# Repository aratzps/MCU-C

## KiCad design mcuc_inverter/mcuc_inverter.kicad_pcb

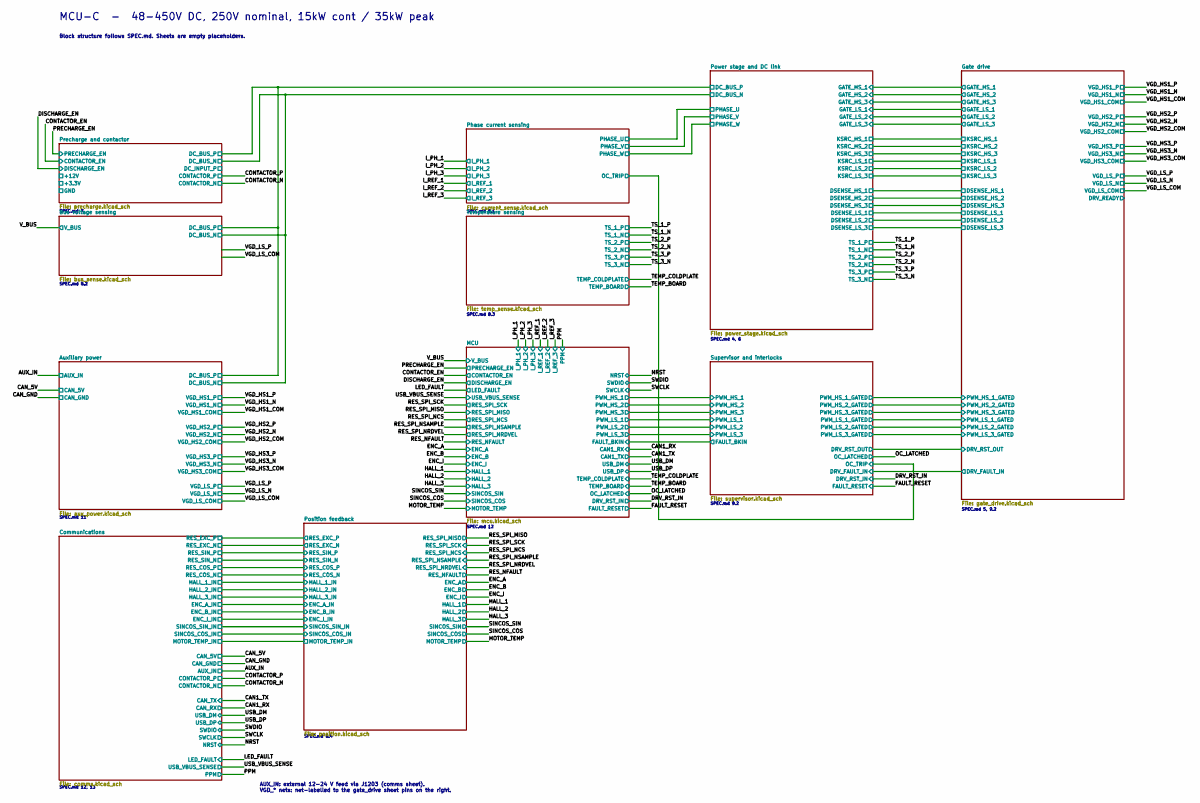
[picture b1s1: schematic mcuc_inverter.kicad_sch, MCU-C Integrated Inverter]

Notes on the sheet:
MCU-C - 48-450V DC, 250V nominal, 15kW cont / 35kW peak
Block structure follows SPEC.md. Sheets are empty placeholders.
SPEC.md 4, 6
SPEC.md 5, 9.2
SPEC.md 7
SPEC.md 8.1
SPEC.md 8.2
SPEC.md 8.3
SPEC.md 8.4
SPEC.md 9.2
SPEC.md 11
SPEC.md 12
SPEC.md 12, 13
AUX_IN: external 12-24 V feed via J1203 (comms sheet). VGD_* nets: net-labelled to the gate_drive sheet pins on the right.

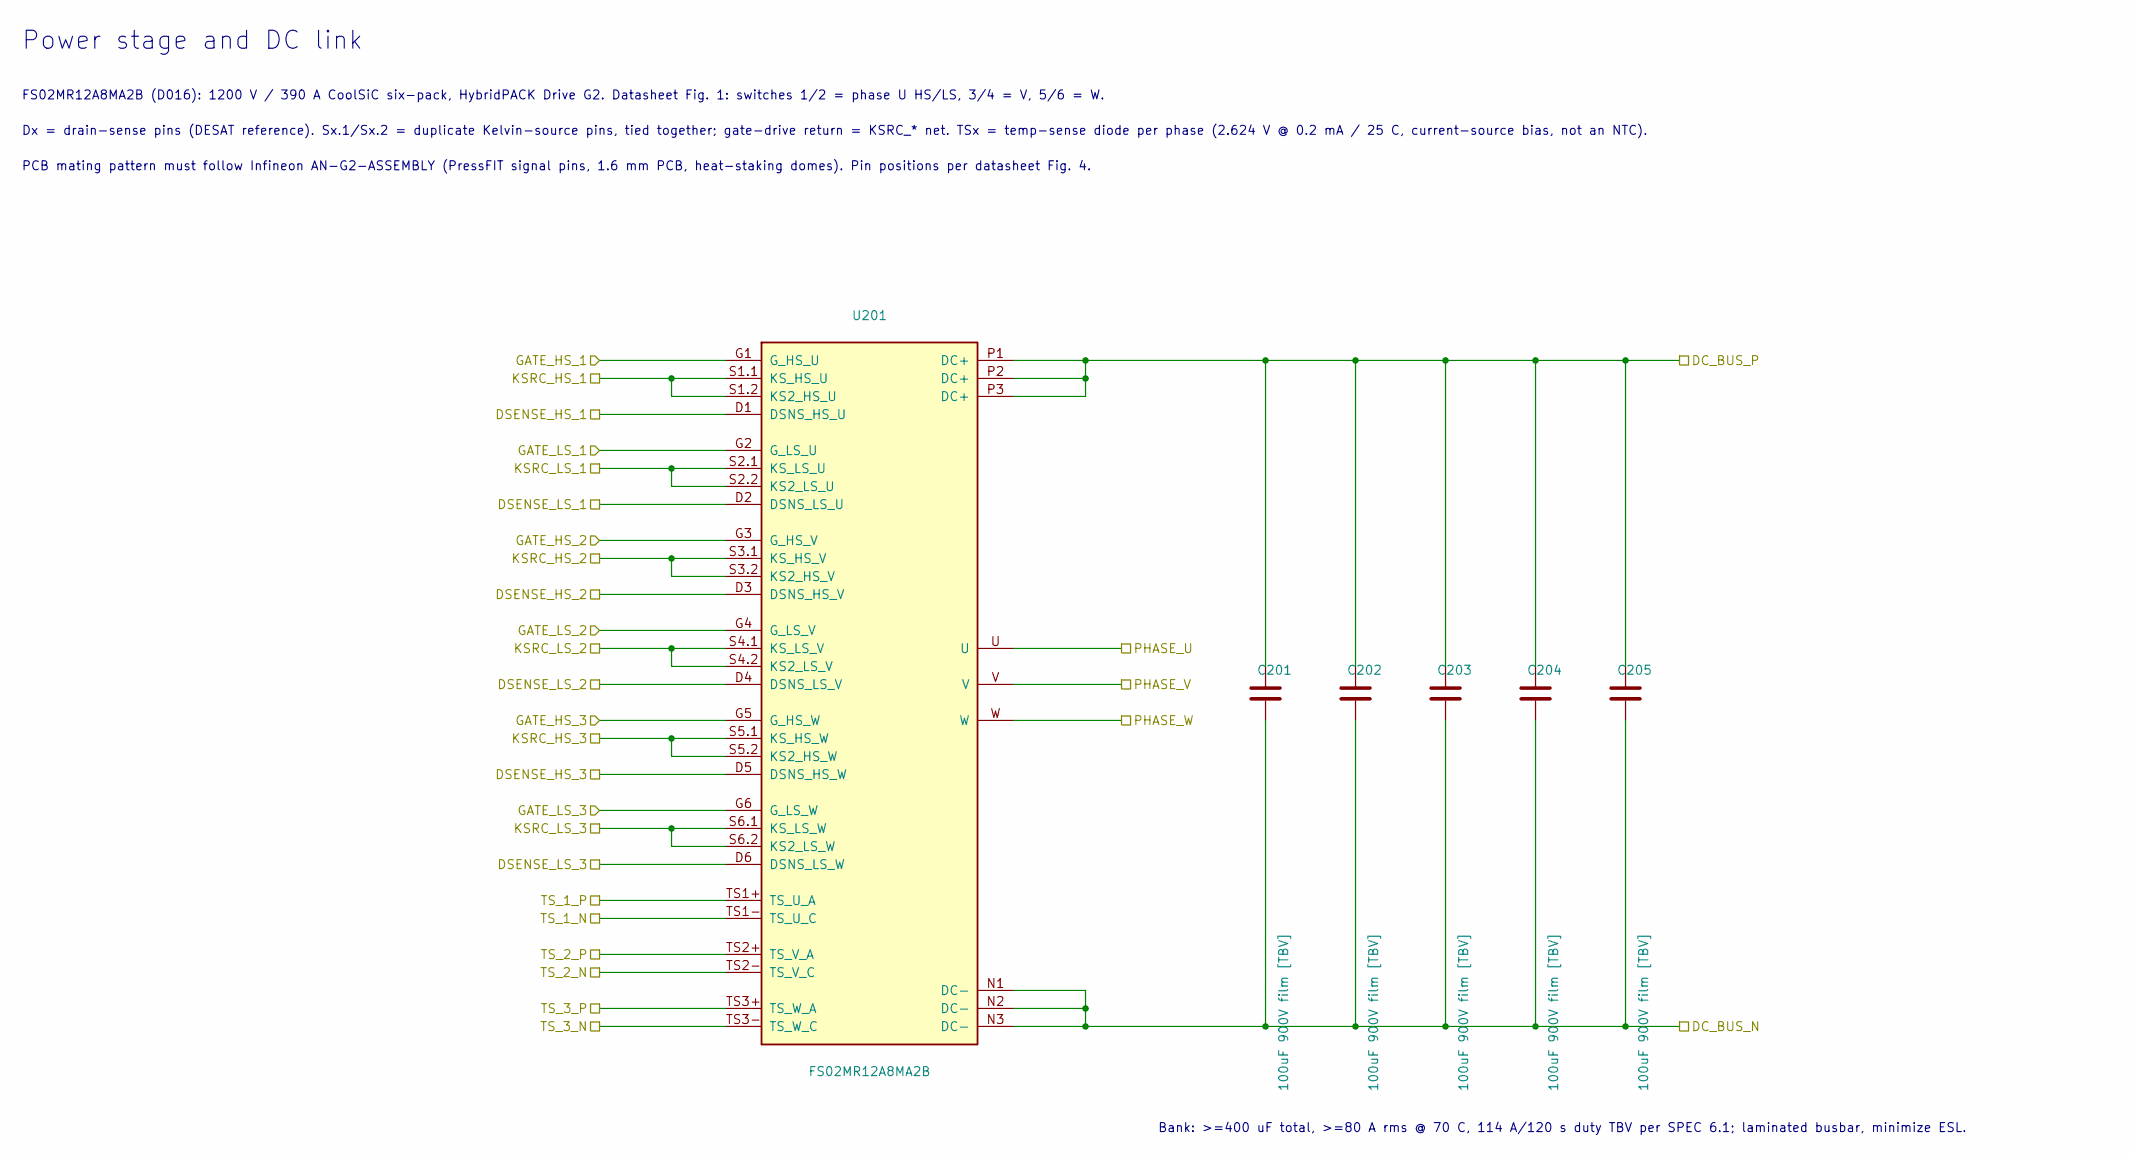
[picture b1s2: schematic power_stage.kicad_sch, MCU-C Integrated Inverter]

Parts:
C201, C202, C203, C204, C205: 100uF 900V film [TBV]; MKP1848C_6pin_52.5x20.3
U201: FS02MR12A8MA2B; FS02MR12A8MA2B_PressFIT

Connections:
/Gate drive/DSENSE_HS_1: U201.D1 (DSNS_HS_U); also elsewhere on the board
/Gate drive/DSENSE_HS_2: U201.D3 (DSNS_HS_V); also elsewhere on the board
/Gate drive/DSENSE_HS_3: U201.D5 (DSNS_HS_W); also elsewhere on the board
/Gate drive/DSENSE_LS_1: U201.D2 (DSNS_LS_U); also elsewhere on the board
/Gate drive/DSENSE_LS_2: U201.D4 (DSNS_LS_V); also elsewhere on the board
/Gate drive/DSENSE_LS_3: U201.D6 (DSNS_LS_W); also elsewhere on the board
/Gate drive/GATE_HS_1: U201.G1 (G_HS_U); also elsewhere on the board
/Gate drive/GATE_HS_2: U201.G3 (G_HS_V); also elsewhere on the board
/Gate drive/GATE_HS_3: U201.G5 (G_HS_W); also elsewhere on the board
/Gate drive/GATE_LS_1: U201.G2 (G_LS_U); also elsewhere on the board
/Gate drive/GATE_LS_2: U201.G4 (G_LS_V); also elsewhere on the board
/Gate drive/GATE_LS_3: U201.G6 (G_LS_W); also elsewhere on the board
/TS_1_N: U201.TS1- (TS_U_C); also elsewhere on the board
/TS_1_P: U201.TS1+ (TS_U_A); also elsewhere on the board
/TS_2_N: U201.TS2- (TS_V_C); also elsewhere on the board
/TS_2_P: U201.TS2+ (TS_V_A); also elsewhere on the board
/TS_3_N: U201.TS3- (TS_W_C); also elsewhere on the board
/TS_3_P: U201.TS3+ (TS_W_A); also elsewhere on the board
/VGD_HS1_COM: U201.S1.1 (KS_HS_U), U201.S1.2 (KS2_HS_U); also elsewhere on the board
/VGD_HS2_COM: U201.S3.1 (KS_HS_V), U201.S3.2 (KS2_HS_V); also elsewhere on the board
/VGD_HS3_COM: U201.S5.1 (KS_HS_W), U201.S5.2 (KS2_HS_W); also elsewhere on the board
/VGD_LS_COM: U201.S2.1 (KS_LS_U), U201.S2.2 (KS2_LS_U), U201.S4.1 (KS_LS_V), U201.S4.2 (KS2_LS_V), U201.S6.1 (KS_LS_W), U201.S6.2 (KS2_LS_W); also elsewhere on the board
unnamed: C201.1, C202.1, C203.1, C204.1, C205.1, U201.P1 (DC+), U201.P2 (DC+), U201.P3 (DC+)
unnamed: C201.2, C202.2, C203.2, C204.2, C205.2, U201.N1 (DC-), U201.N2 (DC-), U201.N3 (DC-)

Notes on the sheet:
Power stage and DC link
FS02MR12A8MA2B (D016): 1200 V / 390 A CoolSiC six-pack, HybridPACK Drive G2. Datasheet Fig. 1: switches 1/2 = phase U HS/LS, 3/4 = V, 5/6 = W.
Dx = drain-sense pins (DESAT reference). Sx.1/Sx.2 = duplicate Kelvin-source pins, tied together; gate-drive return = KSRC_* net. TSx = temp-sense diode per phase (2.624 V @ 0.2 mA / 25 C, current-source bias, not an NTC).
PCB mating pattern must follow Infineon AN-G2-ASSEMBLY (PressFIT signal pins, 1.6 mm PCB, heat-staking domes). Pin positions per datasheet Fig. 4.
Bank: >=400 uF total, >=80 A rms @ 70 C, 114 A/120 s duty TBV per SPEC 6.1; laminated busbar, minimize ESL.

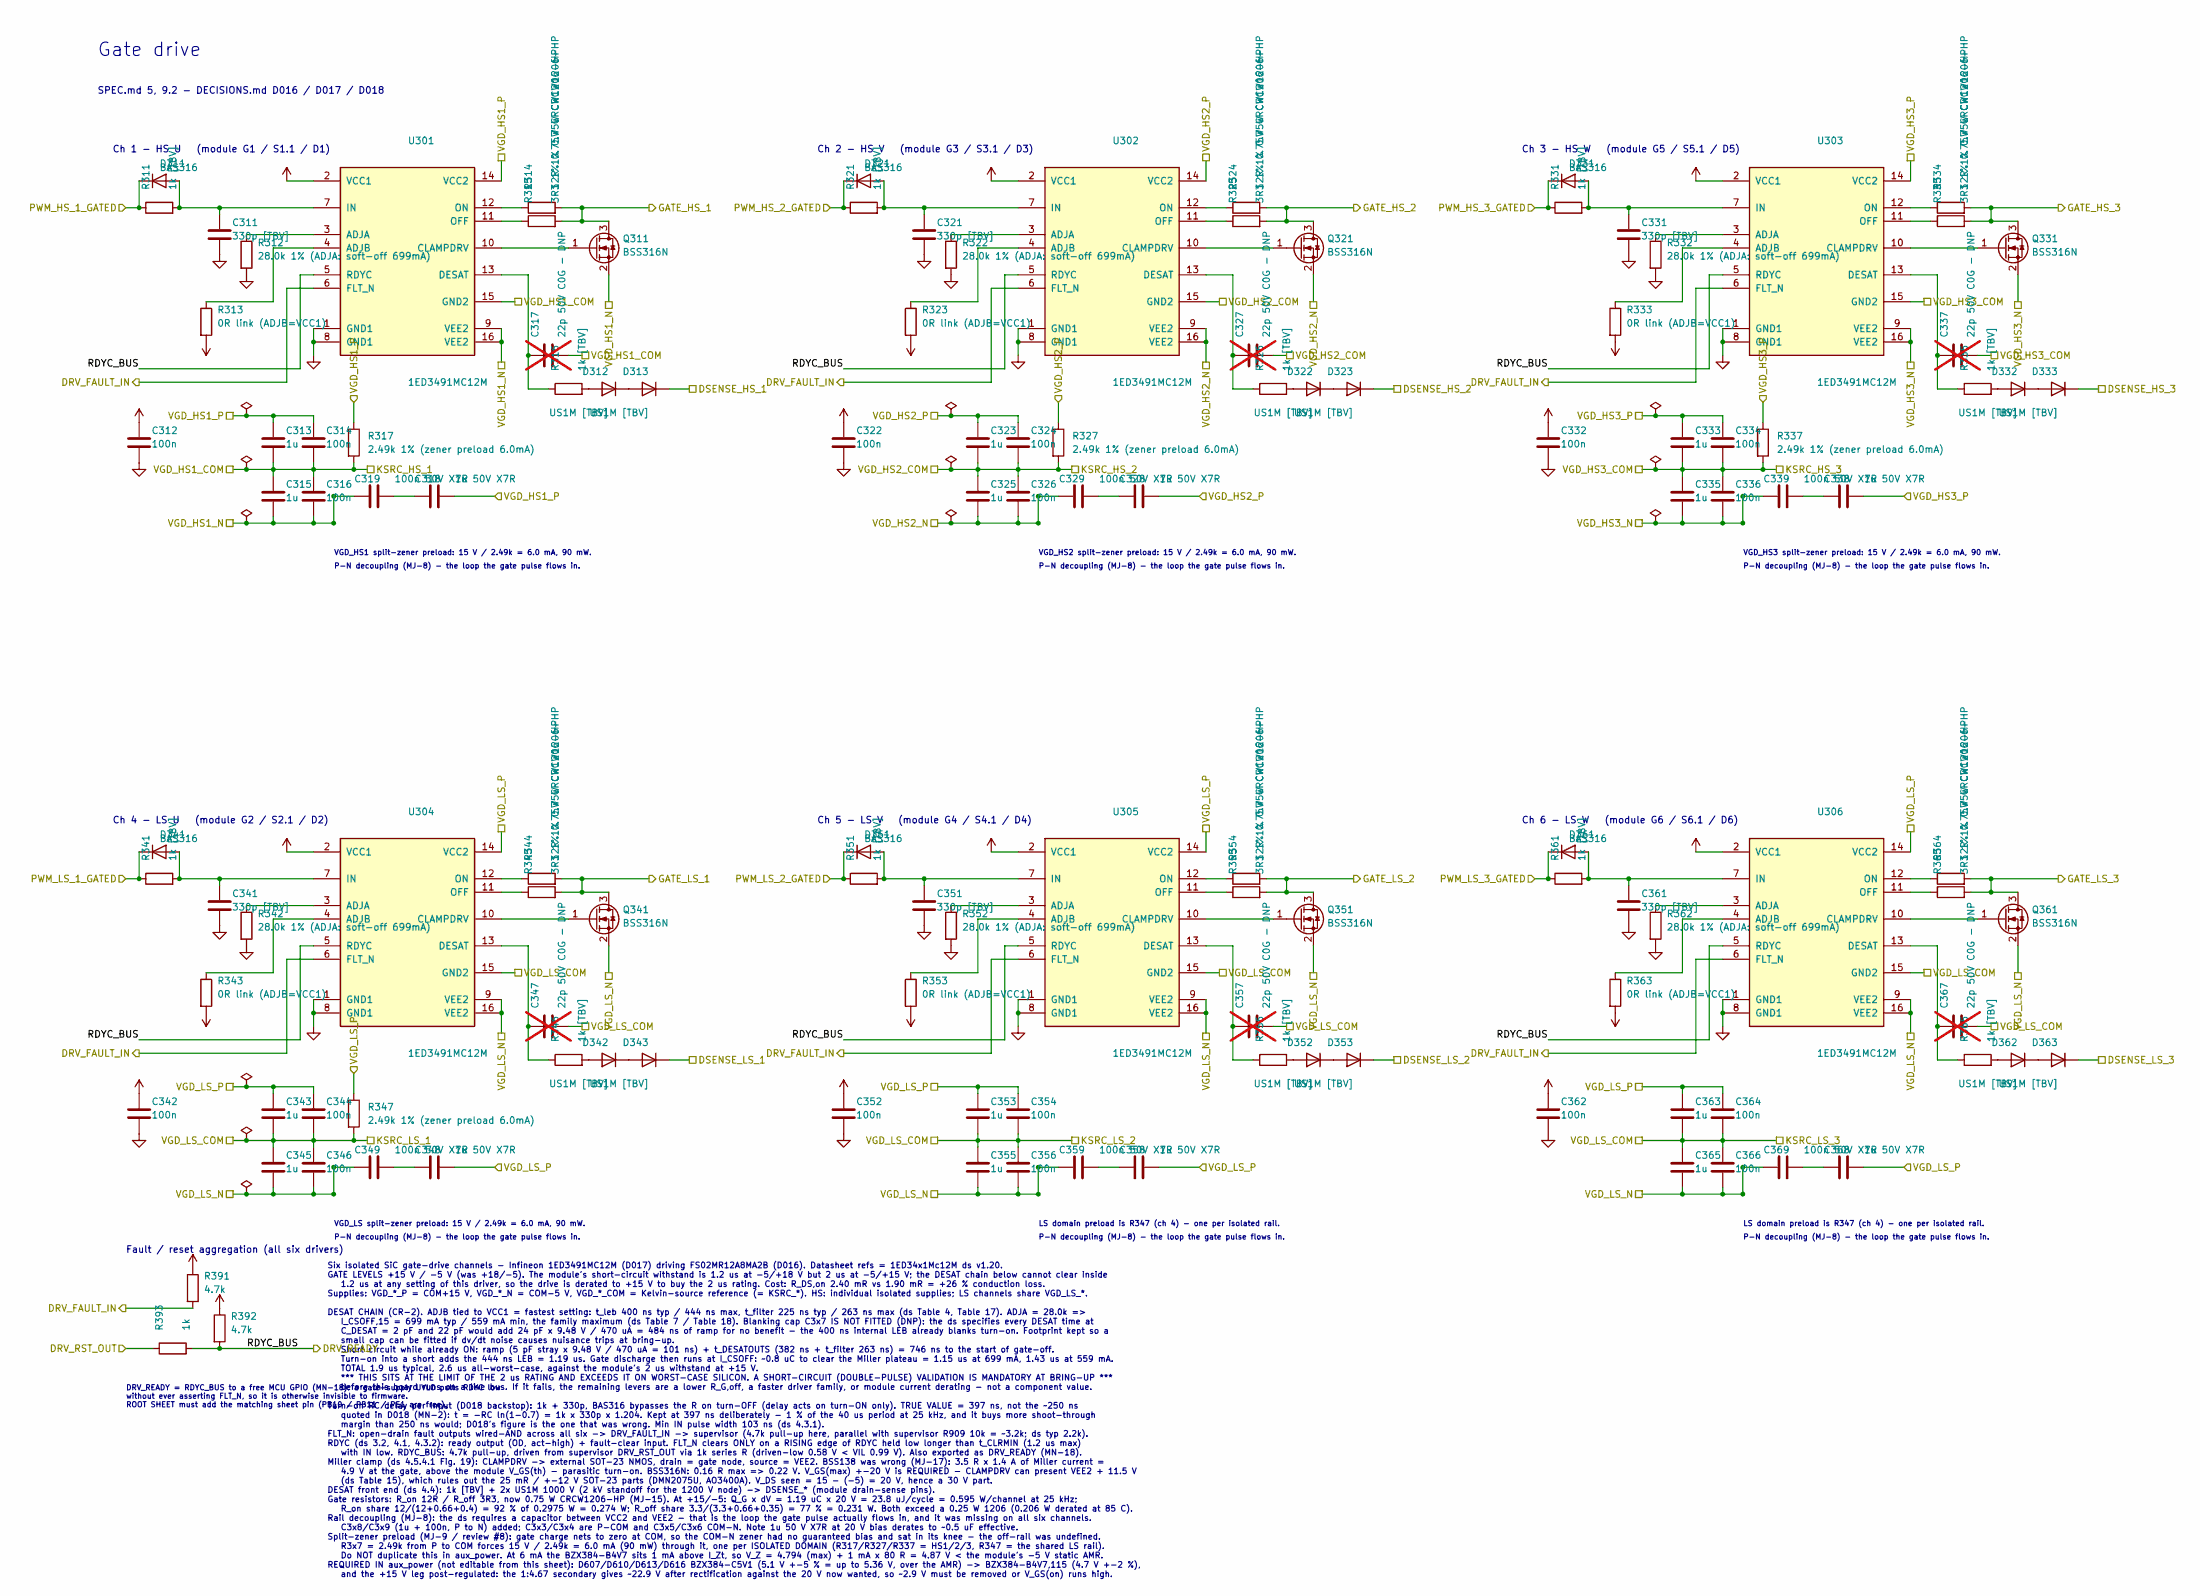
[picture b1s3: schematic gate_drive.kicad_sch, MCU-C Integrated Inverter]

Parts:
C311, C321, C331, C341, C351, C361: 330p [TBV]; C_0603_1608Metric
C312, C314, C316, C322, C324, C326, C332, C334, C336, C342, C344, C346, C352, C354, C356, C362, C364, C366: 100n; C_0603_1608Metric
C313, C315, C323, C325, C333, C335, C343, C345, C353, C355, C363, C365: 1u; C_0805_2012Metric
C317, C327, C337, C347, C357, C367: 22p 50V C0G - DNP; C_0603_1608Metric; not fitted
C318, C328, C338, C348, C358, C368: 1u 50V X7R; C_0805_2012Metric
C319, C329, C339, C349, C359, C369: 100n 50V X7R; C_0603_1608Metric
D311, D321, D331, D341, D351, D361: BAS316; D_SOD-323
D312, D313, D322, D323, D332, D333, D342, D343, D352, D353, D362, D363: US1M [TBV]; D_SMA
Q311, Q321, Q331, Q341, Q351, Q361: BSS316N; SOT-23
R311, R321, R331, R341, R351, R361: 1k [TBV]; R_0603_1608Metric
R312, R322, R332, R342, R352, R362: 28.0k 1% (ADJA: soft-off 699mA); R_0603_1608Metric
R313, R323, R333, R343, R353, R363: 0R link (ADJB=VCC1); R_0603_1608Metric
R314, R324, R334, R344, R354, R364: 12R 1% 0.75W CRCW1206-HP; R_1206_3216Metric
R315, R325, R335, R345, R355, R365: 3R3 1% 0.75W CRCW1206-HP; R_1206_3216Metric
R316, R326, R336, R346, R356, R366: 1k [TBV]; R_1206_3216Metric
R317, R327, R337, R347: 2.49k 1% (zener preload 6.0mA); R_1206_3216Metric
R391, R392: 4.7k; R_0603_1608Metric
R393: 1k; R_0603_1608Metric
U301, U302, U303, U304, U305, U306: 1ED3491MC12M; PG-DSO-16-28

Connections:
/Gate drive/DRV_RST_OUT: R393.1; also elsewhere on the board
/Gate drive/DSENSE_HS_1: D313.1 (K); also elsewhere on the board
/Gate drive/DSENSE_HS_2: D323.1 (K); also elsewhere on the board
/Gate drive/DSENSE_HS_3: D333.1 (K); also elsewhere on the board
/Gate drive/DSENSE_LS_1: D343.1 (K); also elsewhere on the board
/Gate drive/DSENSE_LS_2: D353.1 (K); also elsewhere on the board
/Gate drive/DSENSE_LS_3: D363.1 (K); also elsewhere on the board
/Gate drive/GATE_HS_1: Q311.3 (D), R314.2, R315.2; also elsewhere on the board
/Gate drive/GATE_HS_2: Q321.3 (D), R324.2, R325.2; also elsewhere on the board
/Gate drive/GATE_HS_3: Q331.3 (D), R334.2, R335.2; also elsewhere on the board
/Gate drive/GATE_LS_1: Q341.3 (D), R344.2, R345.2; also elsewhere on the board
/Gate drive/GATE_LS_2: Q351.3 (D), R354.2, R355.2; also elsewhere on the board
/Gate drive/GATE_LS_3: Q361.3 (D), R364.2, R365.2; also elsewhere on the board
/Gate drive/PWM_HS_1_GATED: D311.1 (K), R311.1; also elsewhere on the board
/Gate drive/PWM_HS_2_GATED: D321.1 (K), R321.1; also elsewhere on the board
/Gate drive/PWM_HS_3_GATED: D331.1 (K), R331.1; also elsewhere on the board
/Gate drive/PWM_LS_1_GATED: D341.1 (K), R341.1; also elsewhere on the board
/Gate drive/PWM_LS_2_GATED: D351.1 (K), R351.1; also elsewhere on the board
/Gate drive/PWM_LS_3_GATED: D361.1 (K), R361.1; also elsewhere on the board
/Gate drive/RDYC_BUS: R392.2, R393.2, U301.5 (RDYC), U302.5 (RDYC), U303.5 (RDYC), U304.5 (RDYC), U305.5 (RDYC), U306.5 (RDYC)
/Supervisor and interlocks/DRV_FAULT_IN: R391.2, U301.6 (FLT_N), U302.6 (FLT_N), U303.6 (FLT_N), U304.6 (FLT_N), U305.6 (FLT_N), U306.6 (FLT_N); also elsewhere on the board
/VGD_HS1_COM: C313.2, C314.2, C315.1, C316.1, C317.2, R317.2, U301.15 (GND2); also elsewhere on the board
/VGD_HS1_N: C315.2, C316.2, C319.1, Q311.2 (S), U301.9 (VEE2), U301.16 (VEE2); also elsewhere on the board
/VGD_HS1_P: C313.1, C314.1, C318.2, R317.1, U301.14 (VCC2); also elsewhere on the board
/VGD_HS2_COM: C323.2, C324.2, C325.1, C326.1, C327.2, R327.2, U302.15 (GND2); also elsewhere on the board
/VGD_HS2_N: C325.2, C326.2, C329.1, Q321.2 (S), U302.9 (VEE2), U302.16 (VEE2); also elsewhere on the board
/VGD_HS2_P: C323.1, C324.1, C328.2, R327.1, U302.14 (VCC2); also elsewhere on the board
/VGD_HS3_COM: C333.2, C334.2, C335.1, C336.1, C337.2, R337.2, U303.15 (GND2); also elsewhere on the board
/VGD_HS3_N: C335.2, C336.2, C339.1, Q331.2 (S), U303.9 (VEE2), U303.16 (VEE2); also elsewhere on the board
/VGD_HS3_P: C333.1, C334.1, C338.2, R337.1, U303.14 (VCC2); also elsewhere on the board
/VGD_LS_COM: C343.2, C344.2, C345.1, C346.1, C347.2, C353.2, C354.2, C355.1, C356.1, C357.2, C363.2, C364.2, C365.1, C366.1, C367.2, R347.2, U304.15 (GND2), U305.15 (GND2), U306.15 (GND2); also elsewhere on the board
/VGD_LS_N: C345.2, C346.2, C349.1, C355.2, C356.2, C359.1, C365.2, C366.2, C369.1, Q341.2 (S), Q351.2 (S), Q361.2 (S), U304.9 (VEE2), U304.16 (VEE2), U305.9 (VEE2), U305.16 (VEE2), U306.9 (VEE2), U306.16 (VEE2); also elsewhere on the board
/VGD_LS_P: C343.1, C344.1, C348.2, C353.1, C354.1, C358.2, C363.1, C364.1, C368.2, R347.1, U304.14 (VCC2), U305.14 (VCC2), U306.14 (VCC2); also elsewhere on the board
GND: C311.2, C312.2, C321.2, C322.2, C331.2, C332.2, C341.2, C342.2, C351.2, C352.2, C361.2, C362.2, R312.2, R322.2, R332.2, R342.2, R352.2, R362.2, U301.1 (GND1), U301.8 (GND1), U302.1 (GND1), U302.8 (GND1), U303.1 (GND1), U303.8 (GND1), U304.1 (GND1), U304.8 (GND1), U305.1 (GND1), U305.8 (GND1), U306.1 (GND1), U306.8 (GND1); also elsewhere on the board
unnamed: C318.1, C319.2
unnamed: C328.1, C329.2
unnamed: C338.1, C339.2
unnamed: C348.1, C349.2
unnamed: C358.1, C359.2
unnamed: C368.1, C369.2
unnamed: C311.1, D311.2 (A), R311.2, U301.7 (IN)
unnamed: D312.2 (A), R316.2
unnamed: D312.1 (K), D313.2 (A)
unnamed: C321.1, D321.2 (A), R321.2, U302.7 (IN)
unnamed: D322.2 (A), R326.2
unnamed: D322.1 (K), D323.2 (A)
unnamed: C331.1, D331.2 (A), R331.2, U303.7 (IN)
unnamed: D332.2 (A), R336.2
unnamed: D332.1 (K), D333.2 (A)
unnamed: C341.1, D341.2 (A), R341.2, U304.7 (IN)
unnamed: D342.2 (A), R346.2
unnamed: D342.1 (K), D343.2 (A)
unnamed: C351.1, D351.2 (A), R351.2, U305.7 (IN)
unnamed: D352.2 (A), R356.2
unnamed: D352.1 (K), D353.2 (A)
unnamed: C361.1, D361.2 (A), R361.2, U306.7 (IN)
unnamed: D362.2 (A), R366.2
unnamed: D362.1 (K), D363.2 (A)
unnamed: Q311.1 (G), U301.10 (CLAMPDRV)
unnamed: Q321.1 (G), U302.10 (CLAMPDRV)
unnamed: Q331.1 (G), U303.10 (CLAMPDRV)
unnamed: Q341.1 (G), U304.10 (CLAMPDRV)
unnamed: Q351.1 (G), U305.10 (CLAMPDRV)
unnamed: Q361.1 (G), U306.10 (CLAMPDRV)
unnamed: R312.1, U301.3 (ADJA)
unnamed: R313.1, U301.4 (ADJB)
unnamed: C317.1, R316.1, U301.13 (DESAT)
unnamed: R315.1, U301.11 (OFF)
unnamed: R314.1, U301.12 (ON)
unnamed: R322.1, U302.3 (ADJA)
unnamed: R323.1, U302.4 (ADJB)
unnamed: C327.1, R326.1, U302.13 (DESAT)
unnamed: R325.1, U302.11 (OFF)
unnamed: R324.1, U302.12 (ON)
unnamed: R332.1, U303.3 (ADJA)
unnamed: R333.1, U303.4 (ADJB)
unnamed: C337.1, R336.1, U303.13 (DESAT)
unnamed: R335.1, U303.11 (OFF)
unnamed: R334.1, U303.12 (ON)
unnamed: R342.1, U304.3 (ADJA)
unnamed: R343.1, U304.4 (ADJB)
unnamed: C347.1, R346.1, U304.13 (DESAT)
unnamed: R345.1, U304.11 (OFF)
unnamed: R344.1, U304.12 (ON)
unnamed: R352.1, U305.3 (ADJA)
unnamed: R353.1, U305.4 (ADJB)
unnamed: C357.1, R356.1, U305.13 (DESAT)
unnamed: R355.1, U305.11 (OFF)
unnamed: R354.1, U305.12 (ON)
unnamed: R362.1, U306.3 (ADJA)
unnamed: R363.1, U306.4 (ADJB)
unnamed: C367.1, R366.1, U306.13 (DESAT)
unnamed: R365.1, U306.11 (OFF)
unnamed: R364.1, U306.12 (ON)

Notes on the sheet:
Gate drive
SPEC.md 5, 9.2 - DECISIONS.md D016 / D017 / D018
Six isolated SiC gate-drive channels - Infineon 1ED3491MC12M (D017) driving FS02MR12A8MA2B (D016). Datasheet refs = 1ED34x1Mc12M ds v1.20. GATE LEVELS +15 V / -5 V (was +18/-5). The module's short-circuit withstand is 1.2 us at -5/+18 V but 2 us at -5/+15 V; the DESAT chain below cannot clear insid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
Ch 1 - HS U (module G1 / S1.1 / D1)
Ch 2 - HS V (module G3 / S3.1 / D3)
Ch 3 - HS W (module G5 / S5.1 / D5)
Ch 4 - LS U (module G2 / S2.1 / D2)
Ch 5 - LS V (module G4 / S4.1 / D4)
Ch 6 - LS W (module G6 / S6.1 / D6)
Fault / reset aggregation (all six drivers)
VGD_HS1 split-zener preload: 15 V / 2.49k = 6.0 mA, 90 mW.
P-N decoupling (MJ-8) - the loop the gate pulse flows in.
VGD_HS2 split-zener preload: 15 V / 2.49k = 6.0 mA, 90 mW.
VGD_HS3 split-zener preload: 15 V / 2.49k = 6.0 mA, 90 mW.
VGD_LS split-zener preload: 15 V / 2.49k = 6.0 mA, 90 mW.
LS domain preload is R347 (ch 4) - one per isolated rail.
DRV_READY = RDYC_BUS to a free MCU GPIO (MN-18): a gate-supply UVLO pulls RDYC low without ever asserting FLT_N, so it is otherwise invisible to firmware. ROOT SHEET must add the matching sheet pin (PB10 / PB11 / PE1 are free).

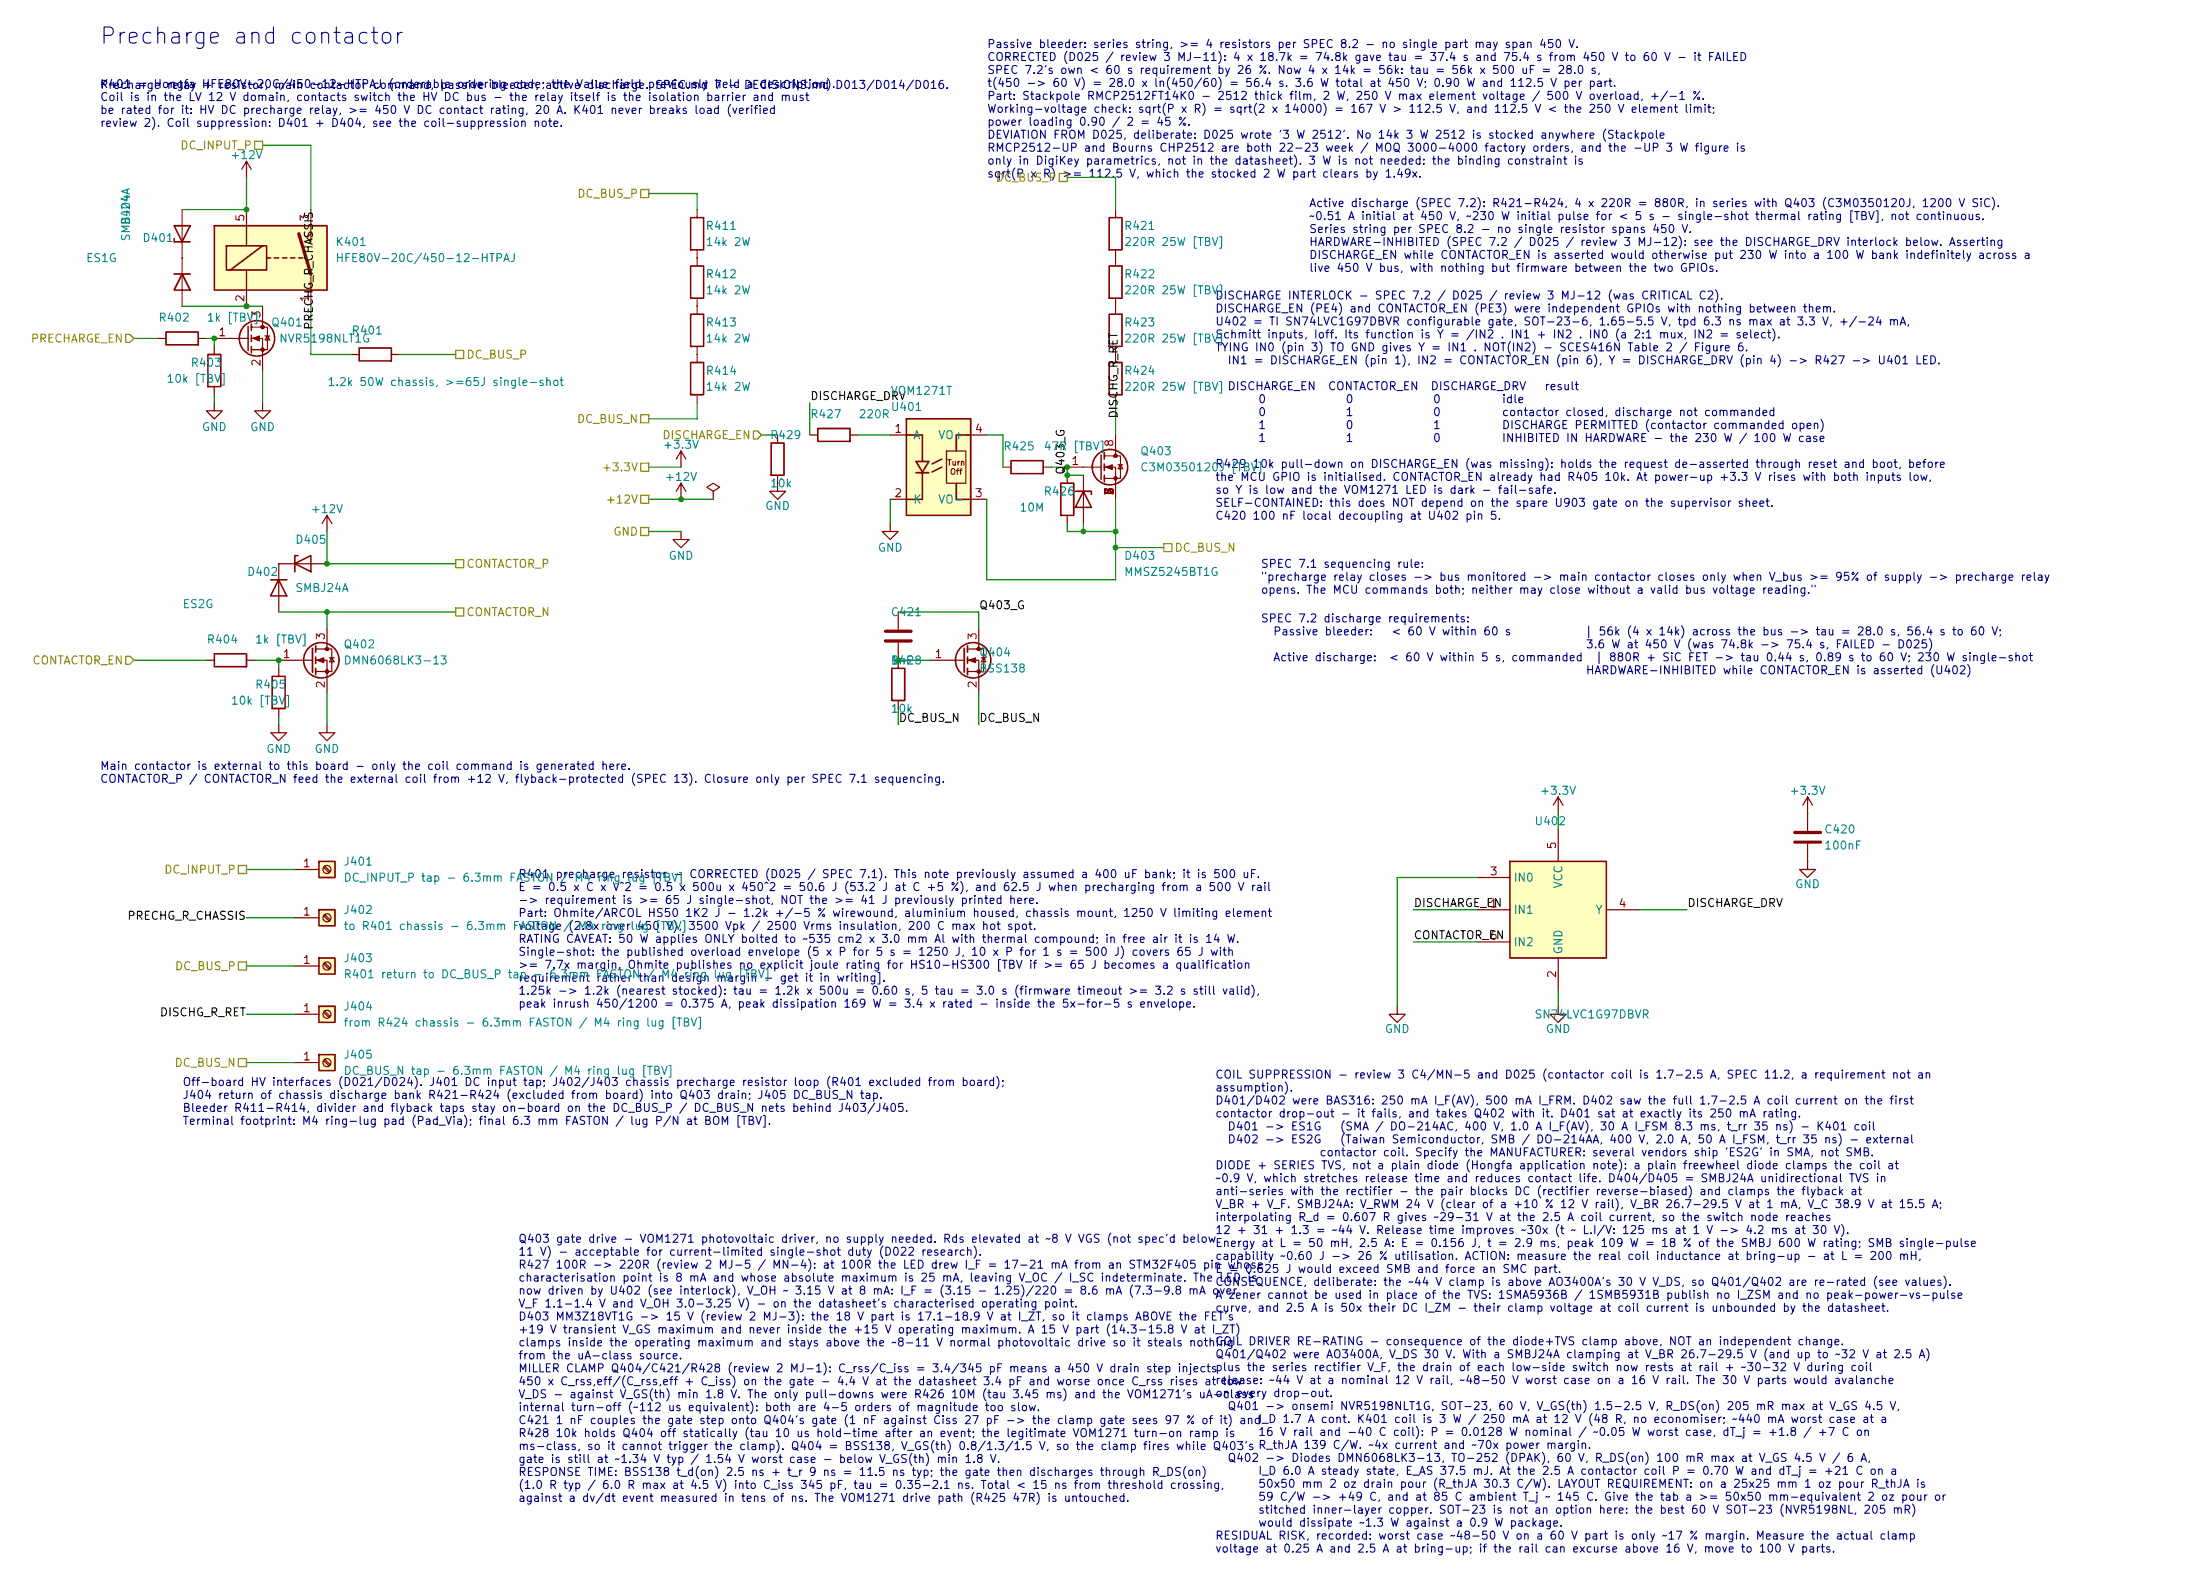
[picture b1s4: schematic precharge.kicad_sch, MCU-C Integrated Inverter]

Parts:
C420: 100nF; C_0603_1608Metric
C421: 1nF; C_0603_1608Metric
D401: ES1G; D_SMA
D402: ES2G; D_SMB
D403: MMSZ5245BT1G; D_SOD-123
D404, D405: SMBJ24A; D_SMB
J401: DC_INPUT_P tap - 6.3mm FASTON / M4 ring lug [TBV]; MountingHole_4.3mm_M4_Pad_Via
J402: to R401 chassis - 6.3mm FASTON / M4 ring lug [TBV]; MountingHole_4.3mm_M4_Pad_Via
J403: R401 return to DC_BUS_P tap - 6.3mm FASTON / M4 r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; MountingHole_4.3mm_M4_Pad_Via
J404: from R424 chassis - 6.3mm FASTON / M4 ring lug [T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; MountingHole_4.3mm_M4_Pad_Via
J405: DC_BUS_N tap - 6.3mm FASTON / M4 ring lug [TBV]; MountingHole_4.3mm_M4_Pad_Via
K401: HFE80V-20C/450-12-HTPAJ; HFE80V_HTPAJ
Q401: NVR5198NLT1G; SOT-23
Q402: DMN6068LK3-13; TO-252-3_TabPin2
Q403: C3M0350120J [TBV]; TO-263-7_TabPin8
Q404: BSS138; SOT-23
R401: 1.2k 50W chassis, >=65J single-shot
R402, R404: 1k [TBV]; R_0603_1608Metric
R403, R405: 10k [TBV]; R_0603_1608Metric
R411, R412, R413, R414: 14k 2W; R_2512_6332Metric
R421, R422, R423, R424: 220R 25W [TBV]
R425: 47R [TBV]; R_0603_1608Metric
R426: 10M; R_0603_1608Metric
R427: 220R; R_0603_1608Metric
R428, R429: 10k; R_0603_1608Metric
U401: VOM1271T; SOP-4_3.8x4.1mm_P2.54mm
U402: SN74LVC1G97DBVR; SOT-23-6

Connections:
+12V: D404.2 (A), D405.2 (A), K401.5; also elsewhere on the board
/Auxiliary power/DC_BUS_P: J403.1, R401.2, R411.1, R421.1; also elsewhere on the board
/CONTACTOR_EN: R404.1, U402.6 (IN2); also elsewhere on the board
/CONTACTOR_N: D402.2 (A), Q402.3 (D); also elsewhere on the board
/DISCHARGE_EN: R429.1, U402.1 (IN1); also elsewhere on the board
/PRECHARGE_EN: R402.1; also elsewhere on the board
/Precharge and contactor/DC_BUS_N: D403.2 (A), J405.1, Q403.2 (S), Q403.3 (S), Q403.4 (S), Q403.5 (S), Q403.6 (S), Q403.7 (S), Q404.2 (S), R414.2, R426.2, R428.2, U401.3 (VO-); also elsewhere on the board
/Precharge and contactor/DC_INPUT_P: J401.1, K401.3
/Precharge and contactor/DISCHARGE_DRV: R427.1, U402.4 (Y)
/Precharge and contactor/DISCHG_R_RET: J404.1, Q403.8 (D), R424.2
/Precharge and contactor/PRECHG_R_CHASSIS: J402.1, K401.1, R401.1
/Precharge and contactor/Q403_G: C421.1, D403.1 (K), Q403.1 (G), Q404.3 (D), R425.2, R426.1
GND: C420.2, Q401.2 (S), Q402.2 (S), R403.2, R405.2, R429.2, U401.2 (K), U402.2 (GND), U402.3 (IN0); also elsewhere on the board
unnamed: D401.2 (A), K401.2, Q401.3 (D)
unnamed: D401.1 (K), D404.1 (K)
unnamed: D402.1 (K), D405.1 (K)
unnamed: Q401.1 (G), R402.2, R403.1
unnamed: Q402.1 (G), R404.2, R405.1
unnamed: C421.2, Q404.1 (G), R428.1
unnamed: R411.2, R412.1
unnamed: R412.2, R413.1
unnamed: R413.2, R414.1
unnamed: R421.2, R422.1
unnamed: R422.2, R423.1
unnamed: R423.2, R424.1
unnamed: R427.2, U401.1 (A)
unnamed: R425.1, U401.4 (VO+)

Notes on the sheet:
Precharge and contactor
Precharge relay + resistor, main contactor command, passive bleeder, active discharge. SPEC.md 7 - DECISIONS.md D013/D014/D016.
K401 = Hongfa HFE80V-20C/450-12-HTPAJ (orderable ordering code; the Value field previously held a description). Coil is in the LV 12 V domain, contacts switch the HV DC bus - the relay itself is the isolation barrier and must be rated for it: HV DC precharge relay, >= 450 V DC contact rating, 20 A.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
R401 precharge resistor - CORRECTED (D025 / SPEC 7.1). This note previously assumed a 400 uF bank; it is 500 uF. E = 0.5 x C x V^2 = 0.5 x 500u x 450^2 = 50.6 J (53.2 J at C +5 %), and 62.5 J when precharging from a 500 V rail -> requirement is >= 65 J single-shot, NOT the >= 41 J previously printe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
Main contactor is external to this board - only the coil command is generated here. CONTACTOR_P / CONTACTOR_N feed the external coil from +12 V, flyback-protected (SPEC 13). Closure only per SPEC 7.1 sequencing.
Passive bleeder: series string, >= 4 resistors per SPEC 8.2 - no single part may span 450 V. CORRECTED (D025 / review 3 MJ-11): 4 x 18.7k = 74.8k gave tau = 37.4 s and 75.4 s from 450 V to 60 V - it FAILED SPEC 7.2's own < 60 s requirement by 26 %. Now 4 x 14k = 56k: tau = 56k x 500 uF = 28.0 s, t(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
Active discharge (SPEC 7.2): R421-R424, 4 x 220R = 880R, in series with Q403 (C3M0350120J, 1200 V SiC). ~0.51 A initial at 450 V, ~230 W initial pulse for < 5 s - single-shot thermal rating [TBV], not continuous. Series string per SPEC 8.2 - no single resistor spans 450 V. HARDWARE-INHIBITED (SPEC 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
Q403 gate drive - VOM1271 photovoltaic driver, no supply needed. Rds elevated at ~8 V VGS (not spec'd below 11 V) - acceptable for current-limited single-shot duty (D022 research). R427 100R -> 220R (review 2 MJ-5 / MN-4): at 100R the LED drew I_F = 17-21 mA from an STM32F405 pin whose characterisa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
SPEC 7.1 sequencing rule: "precharge relay closes -> bus monitored -> main contactor closes only when V_bus >= 95% of supply -> precharge relay opens. The MCU commands both; neither may close without a valid bus voltage reading."
SPEC 7.2 discharge requirements: Passive bleeder: < 60 V within 60 s | 56k (4 x 14k) across the bus -> tau = 28.0 s, 56.4 s to 60 V; 3.6 W at 450 V (was 74.8k -> 75.4 s, FAILED - D025) Active discharge: < 60 V within 5 s, commanded | 880R + SiC FET -> tau 0.44 s, 0.89 s to 60 V; 230 W single-shot H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
Off-board HV interfaces (D021/D024). J401 DC input tap; J402/J403 chassis precharge resistor loop (R401 excluded from board); J404 return of chassis discharge bank R421-R424 (excluded from board) into Q403 drain; J405 DC_BUS_N tap. Bleeder R411-R414, divider and flyback taps stay on-board on the DC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
DISCHARGE INTERLOCK - SPEC 7.2 / D025 / review 3 MJ-12 (was CRITICAL C2). DISCHARGE_EN (PE4) and CONTACTOR_EN (PE3) were independent GPIOs with nothing between them. U402 = TI SN74LVC1G97DBVR configurable gate, SOT-23-6, 1.65-5.5 V, tpd 6.3 ns max at 3.3 V, +/-24 mA, Schmitt inputs, Ioff. Its funct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
COIL SUPPRESSION - review 3 C4/MN-5 and D025 (contactor coil is 1.7-2.5 A, SPEC 11.2, a requirement not an assumption). D401/D402 were BAS316: 250 mA I_F(AV), 500 mA I_FRM. D402 saw the full 1.7-2.5 A coil current on the first contactor drop-out - it fails, and takes Q402 with it. D401 sat at exact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
COIL DRIVER RE-RATING - consequence of the diode+TVS clamp above, NOT an independent change. Q401/Q402 were AO3400A, V_DS 30 V. With a SMBJ24A clamping at V_BR 26.7-29.5 V (and up to ~32 V at 2.5 A) plus the series rectifier V_F, the drain of each low-side switch now rests at rail + ~30-32 V during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
